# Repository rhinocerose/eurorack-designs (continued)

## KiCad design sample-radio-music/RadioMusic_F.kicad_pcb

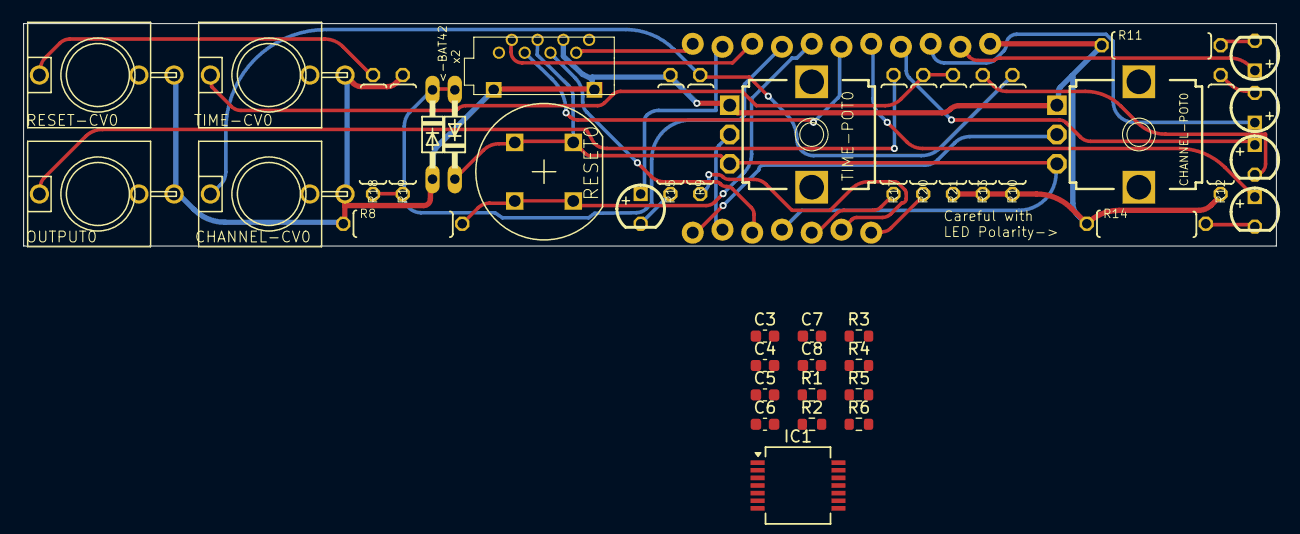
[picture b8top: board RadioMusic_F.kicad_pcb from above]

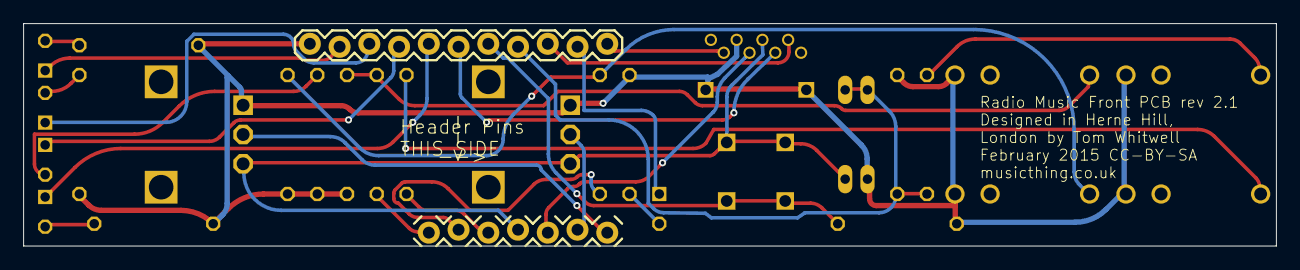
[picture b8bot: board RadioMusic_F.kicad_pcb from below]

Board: 4 copper layers, 107.0 x 19.0 mm, 43 parts (2 on the bottom side), 38 nets.

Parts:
C3, C4, C5, C8: 100n; C_0603_1608Metric
C6, C7: 1n; C_0603_1608Metric
CHANNEL-CV0: WQP-PJ301M-12_JACK
CHANNEL-POT0: 50k; EVUF
D7, D8: BAT42; DO34-7
IC1: TL074; SSOP-14_5.3x6.2mm_P0.65mm
JP2: M11LOCK; 1X11_LOCK
JP4: M07LOCK; 1X07_LOCK
LED1, LED2, LED3, LED4, LED5: LED3MM
OUTPUT0: WQP-PJ301M-12_JACK
R1, R2: 47R; R_0603_1608Metric
R3, R4: 8.2k; R_0603_1608Metric
R5: 330K; R_0603_1608Metric
R6: 1k; R_0603_1608Metric
R8: 10k; 0207_10
R9, R20: 22k; 0207_10
R10, R21: 47k; 0207_10
R11, R12, R13, R14, R15: 1.5k; 0207_10
R17, R18: 220R; 0207_10
R19: 100k; 0207_10
RESET0: D6_PUSH_SWITCH; D6_BUTTON_RND
RESET-CV0: WQP-PJ301M-12_JACK
TIME-CV0: WQP-PJ301M-12_JACK
TIME-POT0: 50k; EVUF
X1: VERT_SD_CARD_REV2; VERT_MICROSD_REV2

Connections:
+12V: C3.2, IC1.4 (V+)
-12V: C4.2, IC1.11 (V-)
/+3.3V_F: CHANNEL-POT0.3 (E), D7.C, JP4.4, RESET0.P$3, RESET0.P$4, TIME-POT0.3 (E), X1.P$4 (VCC/+)
/AUDIO_OUT_F: JP4.5, R17.1
/CHANNEL_CV_F: JP4.6, R9.1
/CHANNEL_POT_F: CHANNEL-POT0.2 (S), JP4.1
/GND_F: CHANNEL-CV0.P$3 (1), CHANNEL-POT0.1 (A), D8.A, JP2.1, OUTPUT0.P$3 (1), R8.1, R10.1, R11.1, R12.1, R13.1, R14.1, R15.2, R19.2, R21.1, RESET-CV0.P$3 (1), TIME-CV0.P$3 (1), TIME-POT0.1 (A), X1.GND1 (SHIELD@1), X1.GND2 (SHIELD@2), X1.P$6 (GND)
/LED1_F: JP2.2, LED1.A
/LED2_F: JP2.3, LED2.A
/LED3_F: JP2.4, LED3.A
/LED4_F: JP2.5, LED4.A
/LED_RESET_F: JP2.10, LED5.A
/MISO_F: JP2.11, X1.P$7 (DO/MISO)
/MOSI_F: JP2.6, X1.P$3 (DI/MOSI)
/RESET_CV_F: D7.A, D8.C, JP2.8, R18.1, R19.1
/RESET_SW_F: JP2.7, R8.2, RESET0.P$1 (O), RESET0.P$2 (O)
/SCLK_F: JP4.3, X1.P$5 (CLK/SCK)
/SS_F: JP2.9, X1.P$2 (CS/SS)
/TIME_CV_F: JP4.7, R20.1
/TIME_POT_F: JP4.2, TIME-POT0.2 (S)
GND: C3.1, C4.1, C6.2, R5.1, R6.2
unnamed: C5.2, R3.2
unnamed: C7.1, R3.1, R4.1
unnamed: CHANNEL-CV0.P$1 (2), R9.2, R10.2
unnamed: C8.2, IC1.3 (+IN), R5.2
unnamed: IC1.2 (-IN), R6.1
unnamed: IC1.6 (-IN), IC1.7 (OUT), R1.2
unnamed: IC1.8 (OUT), IC1.9 (-IN), R2.2
unnamed: C6.1, IC1.12 (+IN), R4.2
unnamed: C7.2, C8.1, IC1.13 (-IN), IC1.14 (OUT)
unnamed: LED1.K (C), R11.2
unnamed: LED2.K (C), R12.2
unnamed: LED3.K (C), R13.2
unnamed: LED4.K (C), R14.2
unnamed: LED5.K (C), R15.1
unnamed: OUTPUT0.P$1 (2), R17.2
unnamed: R18.2, RESET-CV0.P$1 (2)
unnamed: R20.2, R21.2, TIME-CV0.P$1 (2)

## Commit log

2022-04-20 Fully working!!
2025-08-12 909-work
2025-08-12 Update submodules to track main branch
2025-08-12 Update submodules: set branch=main and fix URLs
2025-08-12 Update submodules: add branch=main and fix URLs
2025-08-13 Remove .gitmodules (no submodules exist)
